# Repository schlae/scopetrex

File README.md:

# SCOPETREX
## Vector Gaming on Your Oscilloscope!

**Update 21-August-2024: I learned that the IRQ line on the 65C22 wasn't connected, so I fixed that.
See the section at the bottom for details, or just fab with the latest files and don't worry about it.**

Have you ever wanted to buy a Vectrex, but you can't afford the high prices on
auction sites? Do you already have a hoard of Vectrexes, but want *another*
one? Well now you can build your own!

The SCOPETREX is basically a Vectrex on a single board without a monitor.
To play games, you have to connect it to an oscilloscope or an XY monitor.

This board is not just an exact clone of a Vectrex; it makes a number of
improvements over the original.

* Single +5V power supply, only 500mA (minimum)
* Configurable X and Y size and polarity
* Configurable brightness and video blanking polarity
* Works with a 68A09/68B09 or the more common 68A09E/68B09E
* Works with the AY-3-8912 sound chip or the cheaper AY-3-8910/YM2149F
* Custom controller board which is also compatible with the Vectrex
* Cool art on the board

All of the components are readily available, either from Mouser or from
various brokers in China. The bills of materials include Mouser part numbers.

[Here is the schematic](https://github.com/schlae/scopetrex/blob/master/Scopetrex.pdf).

There are two separate bills of materials. One is configured for people who
wish to build their SCOPETREX with the 68A09/68B09 (no suffix option), and
the other is configured for the 68A09E/68B09E (note the **E** suffix). In
general, the **E** suffix is easier to find and it is less likely to be a
counterfeit part. One caution: the 6809 and 6809E (no A or B) chips are only
rated to 1MHz while the SCOPETREX requires 1.5MHz operation.

[Bill of Materials, 6809 (plain) version](https://github.com/schlae/scopetrex/blob/master/Scopetrex_6809.csv)

[Bill of Materials, 6809E version](https://github.com/schlae/scopetrex/blob/master/Scopetrex_6809E.csv)

Please note that the 0.1" header pins are *not* listed on the BOM. They are
just standard breakaway headers. Jumper shunts (you will need three) are also
not listed on the BOM.

The game cartridge slot is designed to be used with the Sullins EBC18DRAS
(listed in the BOM as S3311-ND) but you can also use the EDAC 395-036-520-202
since it is available from Mouser and it may be more convenient to order all
the parts at once. If you do this, you will need to install the EDAC slot
at a right angle and add 18 bodge wires (see the Assembly Notes section).

[Here are the fab files](https://github.com/schlae/scopetrex/blob/master/fab/Scopetrex.zip).

Board dimensions are 7 x 5 inches. Order the board in whatever cool colors
you like!

## The Controller
The SCOPETREX also has a controller.

[Schematic](https://github.com/schlae/scopetrex/blob/master/controller/controller.pdf)

[Bill of Materials](https://github.com/schlae/scopetrex/blob/master/controller/controller.csv)

[Fab files](https://github.com/schlae/scopetrex/blob/master/controller/fab/controller.zip)

The board is 5.8 x 2 inches. It's very simple, so before fabbing it out,
considering going into Kicad and customizing it to your tastes. Add some fancy
silkscreen artwork or whatever you want.

The thumb joystick is listed with a Digi-Key part number since Mouser doesn't
carry it, but you can also get it from [Sparkfun](https://www.sparkfun.com/products/9032). There are similar joysticks sold by a number of different vendors
but this is the only one that's been tested.

There is a slide switch with 4 positions that selects which button (1 through
4) the top hat control triggers (when you push down on the joystick).

## Firmware
The SCOPETREX will run with the standard Vectrex firmware. Just program it
into the flash memory chip (the AT28C64). Note that the "Vectrex BIOS" ROM that
you may find does not include the MINE STORM game. Often, the "MINE STORM" ROM
comes with the BIOS so you should use that instead. I will not tell you where
to get ROMs, nor will I send you any. You could go buy a broken Vectrex and
transplant the ROM from that.

## Assembly Notes

In general it is a good idea to socket the chips that are hard to find and
thus may be counterfeit. It makes troubleshooting much easier. Therefore,
consider socketing the 6809, the 65C22, and the AY-3-8910/12.

The U101/MC34063 power supply chip should be soldered directly to the board
for best performance since a socket adds resistance.

The game cartridge connector has two different part numbers on the BOM. If
you ordered the EDAC part from Mouser which is designed to mount vertically
on the board, you will not be able to plug the cart into it because the case
will bump into components on the board. I recommend rotating the connector
90 degrees and soldering the bottom 18 pins directly to the footprint and
connecting the top 18 pins using bodge wires.

Don't forget to install the jumpers J301, J302, and J303. If you aren't sure
what polarity you need, just set them all to "NORM."

Set all the trimmer potentiometers to the halfway position. You'll tune them
later on.

Don't forget to flash the firmware into the AT28C64. There are many devices
that can do this. I like the MINIPRO programmers that are available cheaply
from many different sources.

When you assemble the controller board, be sure to install the DE-9 connector
on the bottom of the circuit board rather than the top.

## Initial Powerup and Calibration
You can connect your oscilloscope probes to the X, Y, and Z (aka blanking)
directly or by making up adapter BNC cables that go directly into your
oscilloscope or XY monitor inputs.

To start with, connect just the X and Y outputs to your oscilloscope's channel
1 and channel 2 inputs. Set both channels to 1V/div and put the oscilloscope
into XY mode (on some oscilloscopes, you do this by rotating the horizontal
sweep rate knob all the way counterclockwise).

**Be very careful about setting the brightness/intensity control on your
oscilloscope. A spot that is too bright can permanently damage the phosphor
coating inside the CRT, leaving a dark spot!**

Connect a 5V power source to the input jack on the SCOPETREX and move the
power switch to the ON position. After a second you should see lines and dots
appear in various places on the oscilloscope. You may have to adjust the
intensity knob to be able to see them.

Next, connect the oscilloscope's Z axis input (sometimes called video or
blanking) to the Z axis output of the SCOPETREX. Try adjusting the brightness
trimmer on the SCOPETREX. If you still see a lot of lines and a bright spot
in the middle of the screen, switch the polarity jumper on the Z axis (JP301).
Adjust the brightness trimmer again until the spot in the center goes away.

At this point you can also plug in a controller and some speakers into the
audio jack. Make sure you can get sound, and check if the controller works.

The SCOPETREX requires some calibration to be performed to get the best image
quality. To do this, you will need a Vectrex test cart (often included in
multicarts, which you probably want to have anyway.)

The first step of calibration involves correcting the DAC offset voltage. With
the test cart installed (no hot swapping carts! label side up!) you will first
see a grid displayed on the screen. Hit button 4, and the display should read
"DAC OFFSET," slowly blinking on and off. Connect a voltmeter between ground
(I like the convenient mounting holes in the corners of the board) and the left
side of R303 (marked with an arrow on the board). This is the voltage output,
pin 1, of the U304 op amp. With the text *off*, the voltmeter should read 0V.
If not, adjust the DAC offset trimmer until you get the voltage to 0V.

The second step involves fixing the X and Y adjustments. You can do this with
the test cart's third screen by pressing button 4 again. You'll see some
diamond-shaped targets; adjust X and Y so that the vertical and horizontal
lines are center inside the diamond shapes.

The third step is less specific, try hitting buttons 3 and 4 to switch to
various screens. Adjust the X and Y as you like to get things to look good.

The final step is the joystick calibration. Go to the last screen--the one
that you can't seem to exit by pushing a button--and adjust the two trimmers
on the *controller board* until the line segment turns into a dot. Swirl the
joystick around to make sure it hits all the square boxes. To exit this screen,
you have to push buttons 1 and 3 or buttons 1 and 4 at the same time.

## XY Monitors

XY monitors such as the Tektronix 602 or 604 offer a nicer experience for
playing Vectrex games. Typically they have a fixed analog deflection voltage of
only a volt or two, so you will need to use the width and height trimmers to
dial back the deflection so that all the objects are on the screen.

Pro tip--turn a landscape-mode XY monitor up on its side and swap the X and Y
inputs to mimic the Vectrex's portrait orientation.

## Troubleshooting
The SCOPETREX is a fairly complex mixed-signal board. I can't tell you all the
possible ways it can go wrong, but here's a list of things to check...
* Power supply voltages: Are +5V, -5V, and the -12V rails all present?
* Reset signal: Does the reset input on the 6809 go high?
* Does the 6809 have a valid set of clock signals? Check E and Q, and the
crystal or oscillator
* Is there activity on the bus? Check the address and data lines
* Does the ROM chip ever get selected? Both the CS# and OE# lines must be
pulsing for that to happen. How about the RAM chip?
* Check for activity on the 65C22 outputs
* Does sound come out of the AY-3-8910/2?
* Look at the waveform on pin 1 of U304A. You should see a fairly complex
waveform
* The SCOPETREX works by using a constant voltage into an integrator to
generate ramps that drive the X and Y deflection signals. Work your way back
along the analog signal chain starting from the individual deflection outputs
* Take a look at the blanking signal (Z axis) output magnitudes. You might
want to check the manual for your oscilloscope to find out the acceptable range
of voltages

## The IRQ Line Bug

Lately it came to my attention that there was a bug in the earlier version of
the board, but nobody actually reported it to me! Fortunately it is a very
easy issue to fix. If you fab your boards from the latest version of the files
in this repository (21-August-2024 or later) then this issue has been fixed.

If you have an older board, you can correct the problem by running a wire from
U207 pin 21 (the 65C22) and U206 pin 3.

## Other Notes

After all that work, don't forget to enjoy playing some Vectrex games!

## License
This work is licensed under a Creative Commons Attribution-ShareAlike 4.0
International License. See [https://creativecommons.org/licenses/by-sa/4.0/](https://creativecommons.org/licenses/by-sa/4.0/).

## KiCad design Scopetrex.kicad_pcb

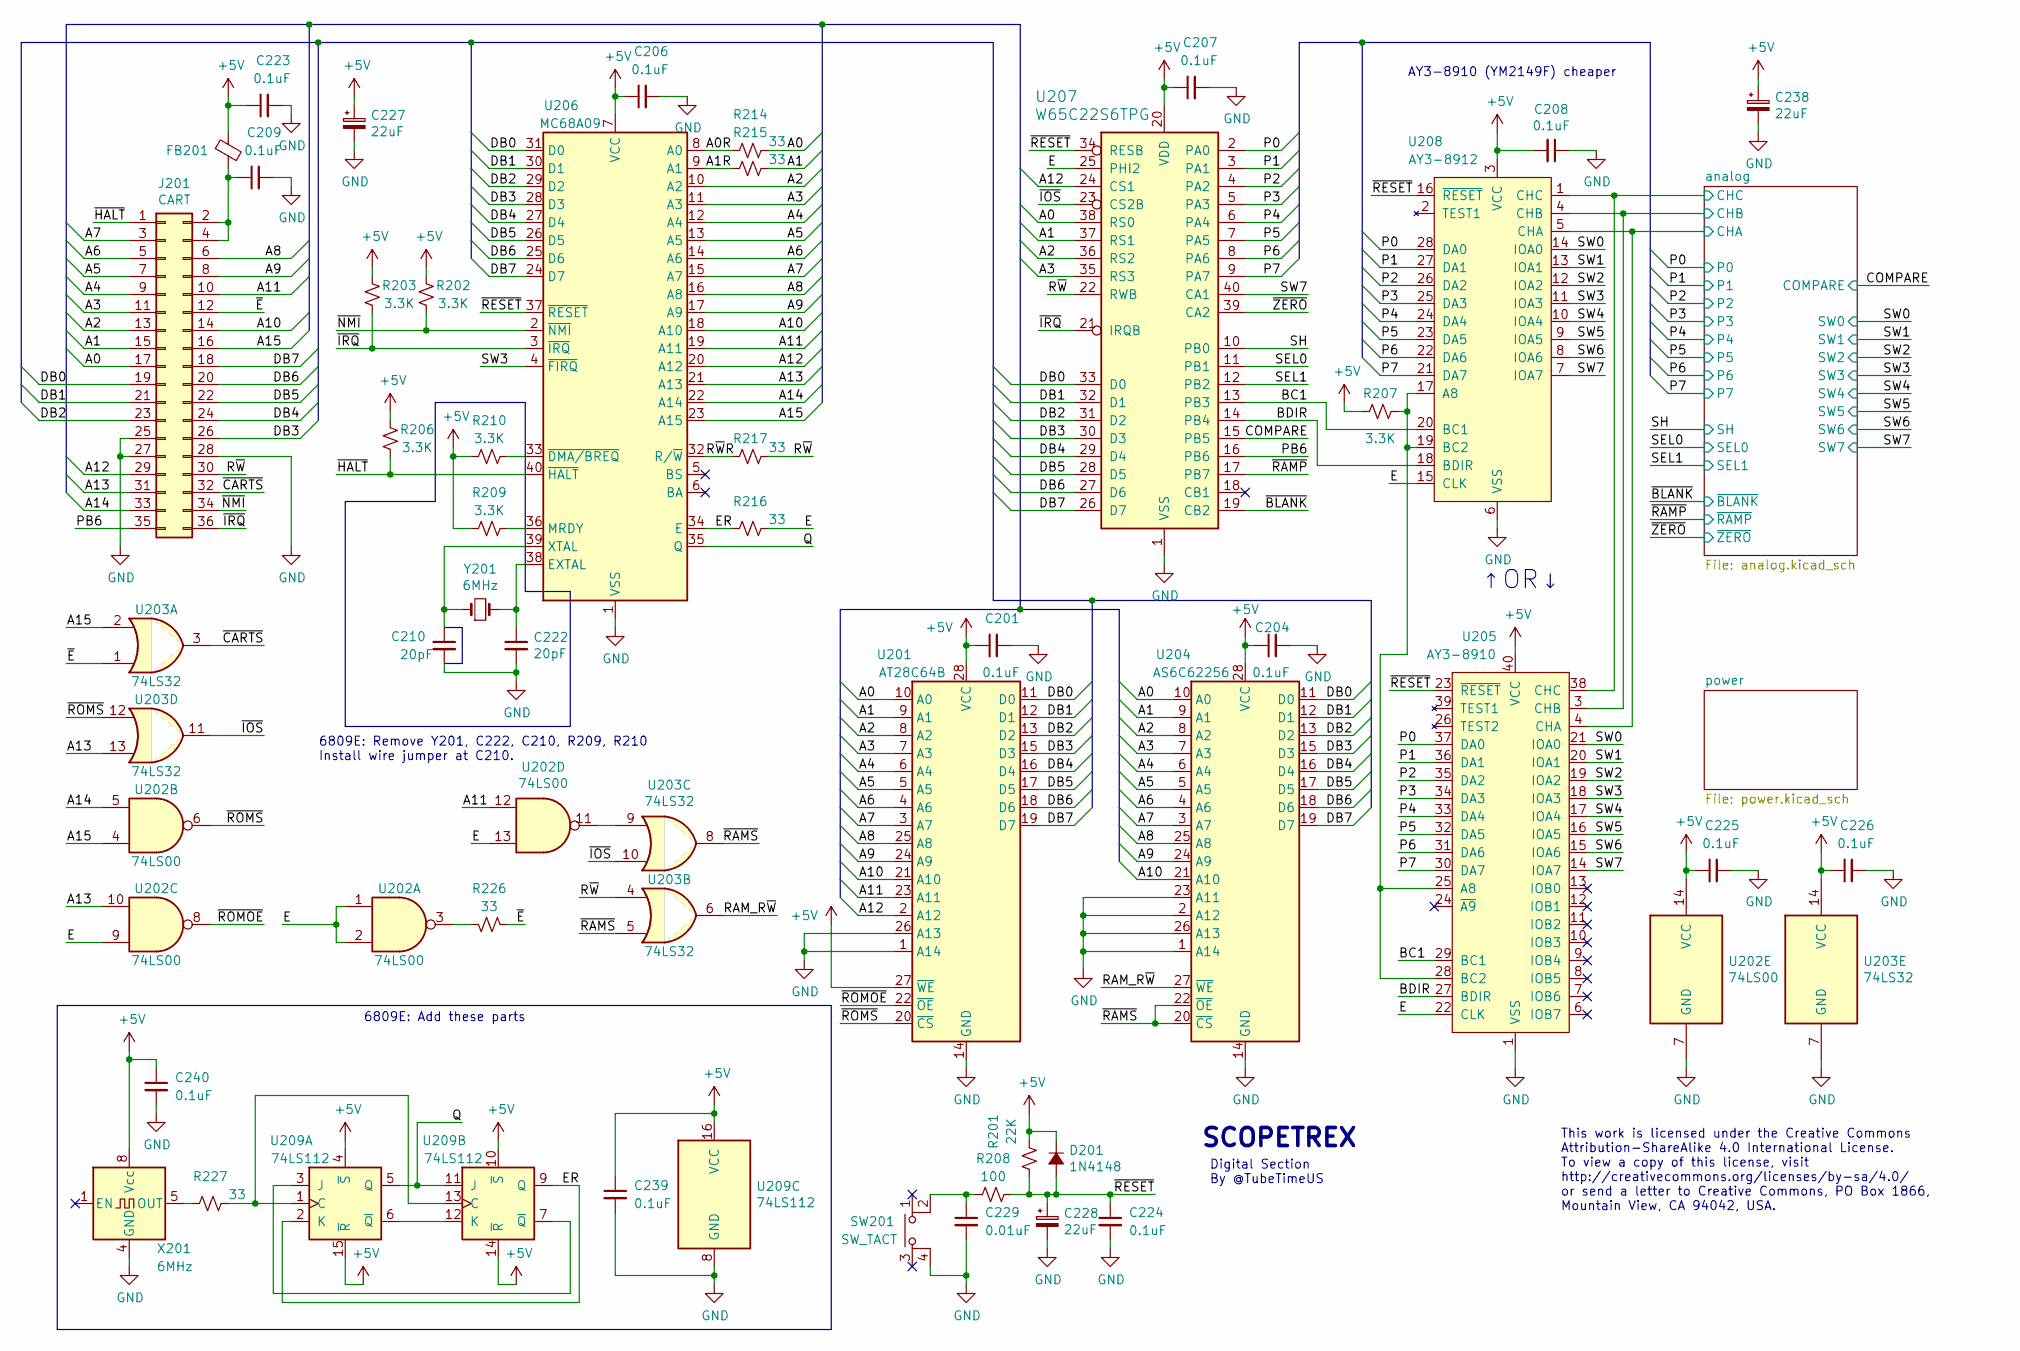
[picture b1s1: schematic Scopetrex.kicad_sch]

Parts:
C201, C204, C206, C207, C208, C209, C223, C224, C225, C226, C239, C240: 0.1uF; C_Disc_D0.2in_W0.1in_P0.2in; Mouser 581-SR215C104K
C210, C222: 20pF; C_Disc_D0.2in_W0.1in_P0.2in; Mouser 581-SR215A220KARTR1
C227, C228, C238: 22uF; CAPAP200; Mouser 647-UPW1A220MDD6TP
C229: 0.01uF; C_Disc_D0.2in_W0.1in_P0.2in; Mouser 581-SR211C103KARTR1
D201: 1N4148; DIOA500; Mouser 512-1N4148
FB201: 96Ω @ 25MHz; FB254; Mouser 623-2743007112
J201: CART; SULLINS_EBC18DRAS; Mouser 587-395-036
R201: 22K; RESA500; Mouser 603-CFR-25JR-5222K
R202, R203, R206, R207, R209, R210: 3.3K; RESA500; Mouser 603-CFR-25JR-523K3
R208: 100; RESA500; Mouser 603-CFR-25JR-52100R
R214, R215, R216, R217, R226, R227: 33; RESA500; Mouser 603-CFR-25JR-5233R
SW201: SW_TACT; ESWITCH_TL1105; Mouser 612-TL1105B
U201: AT28C64B; DIP254P1524X635-28; Mouser 556-AT28C64B15PU
U202: 74LS00; DIP254P762X635-14; Mouser 595-SN74LS00N
U203: 74LS32; DIP254P762X635-14; Mouser 595-SN74LS32N
U204: AS6C62256; DIP254P1524X635-28; Mouser 913-AS6C62256-55PCN
U205: AY3-8910; DIP254P1524X635-40
U206: MC68A09; DIP254P1524X635-40
U207: W65C22S6TPG; DIP254P1524X635-40; Mouser 955-W65C22S6TPG-14
U208: AY3-8912; DIP254P1524X635-28
U209: 74LS112; DIP254P762X635-16; Mouser 595-SN74LS112AN
X201: 6MHz; Oscillator_DIP-8; Mouser 774-MXO45HS-3C-6.0
Y201: 6MHz; Crystal_HC49-4H_Vertical; Mouser 815-AB-6-B2

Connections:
+5V: C201.1, C204.1, C206.1, C207.1, C208.2, C223.1, C225.1, C226.1, C227.1, C238.1, C239.1, C240.1, D201.1 (K), FB201.1, R201.1, R202.2, R203.2, R206.2, R207.2, R209.1, R210.2, U201.27 (~WE), U201.28 (VCC), U202.14 (VCC), U203.14 (VCC), U204.28 (VCC), U205.40 (VCC), U206.7 (VCC), U207.20 (VDD), U208.3 (VCC), U209.4 (~S), U209.10 (~S), U209.14 (~R), U209.15 (~R), U209.16 (VCC), X201.8 (Vcc); also elsewhere on the board
/A0: J201.17, R214.1, U201.10 (A0), U204.10 (A0), U207.38 (RS0)
/A0R: R214.2, U206.8 (A0)
/A1: J201.15, R215.1, U201.9 (A1), U204.9 (A1), U207.37 (RS1)
/A1R: R215.2, U206.9 (A1)
/A2: J201.13, U201.8 (A2), U204.8 (A2), U206.10 (A2), U207.36 (RS2)
/A3: J201.11, U201.7 (A3), U204.7 (A3), U206.11 (A3), U207.35 (RS3)
/A4: J201.9, U201.6 (A4), U204.6 (A4), U206.12 (A4)
/A5: J201.7, U201.5 (A5), U204.5 (A5), U206.13 (A5)
/A6: J201.5, U201.4 (A6), U204.4 (A6), U206.14 (A6)
/A7: J201.3, U201.3 (A7), U204.3 (A7), U206.15 (A7)
/A8: J201.6, U201.25 (A8), U204.25 (A8), U206.16 (A8)
/A9: J201.8, U201.24 (A9), U204.24 (A9), U206.17 (A9)
/A10: J201.14, U201.21 (A10), U204.21 (A10), U206.18 (A10)
/A11: J201.10, U201.23 (A11), U202.12, U206.19 (A11)
/A12: J201.29, U201.2 (A12), U206.20 (A12), U207.24 (CS1)
/A13: J201.31, U202.10, U203.13, U206.21 (A13)
/A14: J201.33, U202.5, U206.22 (A14)
/A15: J201.16, U202.4, U203.2, U206.23 (A15)
/BC1: U205.29 (BC1), U207.13 (PB3), U208.20 (BC1)
/BDIR: U205.27 (BDIR), U207.14 (PB4), U208.18 (BDIR)
/COMPARE: U207.15 (PB5); also elsewhere on the board
/DB0: J201.19, U201.11 (D0), U204.11 (D0), U206.31 (D0), U207.33 (D0)
/DB1: J201.21, U201.12 (D1), U204.12 (D1), U206.30 (D1), U207.32 (D1)
/DB2: J201.23, U201.13 (D2), U204.13 (D2), U206.29 (D2), U207.31 (D2)
/DB3: J201.26, U201.15 (D3), U204.15 (D3), U206.28 (D3), U207.30 (D3)
/DB4: J201.24, U201.16 (D4), U204.16 (D4), U206.27 (D4), U207.29 (D4)
/DB5: J201.22, U201.17 (D5), U204.17 (D5), U206.26 (D5), U207.28 (D5)
/DB6: J201.20, U201.18 (D6), U204.18 (D6), U206.25 (D6), U207.27 (D6)
/DB7: J201.18, U201.19 (D7), U204.19 (D7), U206.24 (D7), U207.26 (D7)
/E: R216.1, U202.1, U202.2, U202.9, U202.13, U205.22 (CLK), U207.25 (PHI2), U208.15 (CLK)
/ER: R216.2, U206.34 (E), U209.2 (K), U209.9 (Q)
/P0: U205.37 (DA0), U207.2 (PA0), U208.28 (DA0); also elsewhere on the board
/P1: U205.36 (DA1), U207.3 (PA1), U208.27 (DA1); also elsewhere on the board
/P2: U205.35 (DA2), U207.4 (PA2), U208.26 (DA2); also elsewhere on the board
/P3: U205.34 (DA3), U207.5 (PA3), U208.25 (DA3); also elsewhere on the board
/P4: U205.33 (DA4), U207.6 (PA4), U208.24 (DA4); also elsewhere on the board
/P5: U205.32 (DA5), U207.7 (PA5), U208.23 (DA5); also elsewhere on the board
/P6: U205.31 (DA6), U207.8 (PA6), U208.22 (DA6); also elsewhere on the board
/P7: U205.30 (DA7), U207.9 (PA7), U208.21 (DA7); also elsewhere on the board
/PB6: J201.35, U207.16 (PB6)
/Q: U206.35 (Q), U209.5 (Q), U209.11 (J)
/RAM_R~W: U203.6, U204.27 (~WE)
/R~W: J201.30, R217.1, U203.4, U207.22 (RWB)
/R~W~R: R217.2, U206.32 (R/~W)
/SEL0: U207.11 (PB1); also elsewhere on the board
/SEL1: U207.12 (PB2); also elsewhere on the board
/SH: U207.10 (PB0); also elsewhere on the board
/SW0: U205.21 (IOA0), U208.14 (IOA0); also elsewhere on the board
/SW1: U205.20 (IOA1), U208.13 (IOA1); also elsewhere on the board
/SW2: U205.19 (IOA2), U208.12 (IOA2); also elsewhere on the board
/SW3: U205.18 (IOA3), U206.4 (~FIRQ), U208.11 (IOA3); also elsewhere on the board
/SW4: U205.17 (IOA4), U208.10 (IOA4); also elsewhere on the board
/SW5: U205.16 (IOA5), U208.9 (IOA5); also elsewhere on the board
/SW6: U205.15 (IOA6), U208.8 (IOA6); also elsewhere on the board
/SW7: U205.14 (IOA7), U207.40 (CA1), U208.7 (IOA7); also elsewhere on the board
/analog/CHA: U205.4 (CHA), U208.5 (CHA); also elsewhere on the board
/analog/CHB: U205.3 (CHB), U208.4 (CHB); also elsewhere on the board
/analog/CHC: U205.38 (CHC), U208.1 (CHC); also elsewhere on the board
/~BLANK: U207.19 (CB2); also elsewhere on the board
/~CARTS: J201.32, U203.3
/~E: J201.12, R226.2, U203.1
/~HALT: J201.1, R206.1, U206.40 (~HALT)
/~IOS: U203.10, U203.11, U207.23 (CS2B)
/~IRQ: J201.36, R203.1, U206.3 (~IRQ), U207.21 (IRQB)
/~NMI: J201.34, R202.1, U206.2 (~NMI)
/~RAMP: U207.17 (PB7); also elsewhere on the board
/~RAMS: U203.5, U203.8, U204.20 (~CS), U204.22 (~OE)
/~RESET: C224.1, C228.1, D201.2 (A), R201.2, R208.1, U205.23 (~RESET), U206.37 (~RESET), U207.34 (RESB), U208.16 (~RESET)
/~ROMOE: U201.22 (~OE), U202.8
/~ROMS: U201.20 (~CS), U202.6, U203.12
/~ZERO: U207.39 (CA2); also elsewhere on the board
GND: C201.2, C204.2, C206.2, C207.2, C208.1, C209.2, C210.2, C222.2, C223.2, C224.2, C225.2, C226.2, C227.2, C228.2, C229.2, C238.2, C239.2, C240.2, J201.25, J201.27, J201.28, SW201.4, U201.1 (A14), U201.14 (GND), U201.26 (A13), U202.7 (GND), U203.7 (GND), U204.1 (A14), U204.2 (A12), U204.14 (GND), U204.23 (A11), U204.26 (A13), U205.1 (VSS), U206.1 (VSS), U207.1 (VSS), U208.6 (VSS), U209.8 (GND), X201.4 (GND); also elsewhere on the board
unnamed: C209.1, FB201.2, J201.2, J201.4
unnamed: C210.1, U206.39 (XTAL), Y201.1
unnamed: C222.1, U206.38 (EXTAL), Y201.2
unnamed: C229.1, R208.2, SW201.2
unnamed: R207.1, U205.25 (A8), U205.28 (BC2), U208.17 (A8), U208.19 (BC2)
unnamed: R209.2, U206.36 (MRDY)
unnamed: R210.1, U206.33 (~DMA/BREQ)
unnamed: R226.1, U202.3
unnamed: R227.1, U209.1 (C), U209.13 (C)
unnamed: R227.2, X201.5 (OUT)
unnamed: U202.11, U203.9
unnamed: U209.3 (J), U209.7 (~Q)
unnamed: U209.6 (~Q), U209.12 (K)

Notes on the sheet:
6809E: Remove Y201, C222, C210, R209, R210 Install wire jumper at C210.
Digital Section By @TubeTimeUS
SCOPETREX
6809E: Add these parts
↑OR↓
This work is licensed under the Creative Commons Attribution-ShareAlike 4.0 International License. To view a copy of this license, visit http://creativecommons.org/licenses/by-sa/4.0/ or send a letter to Creative Commons, PO Box 1866, Mountain View, CA 94042, USA.
AY3-8910 (YM2149F) cheaper

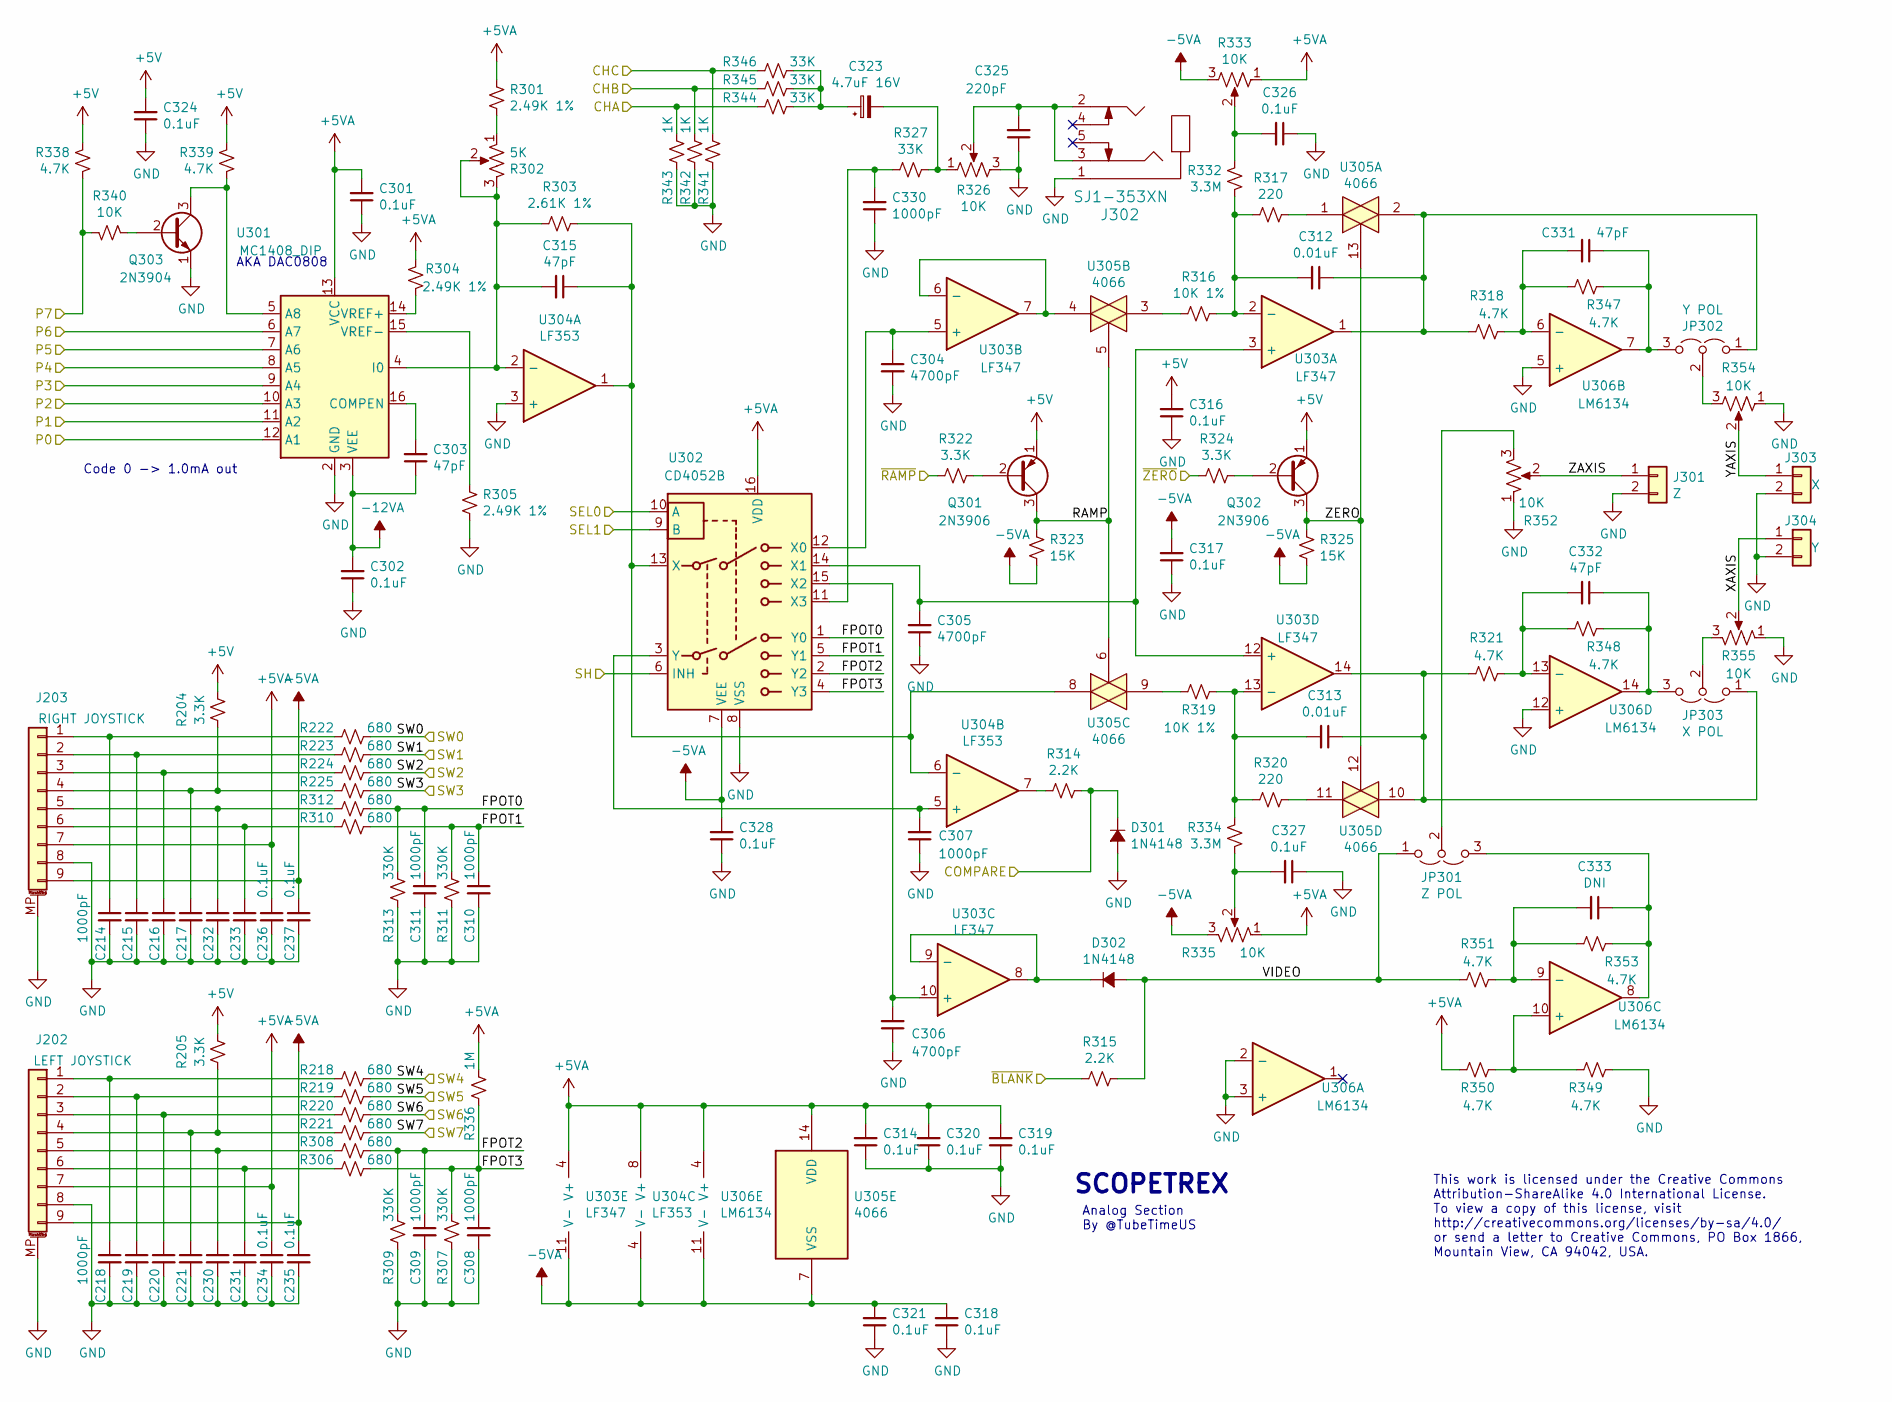
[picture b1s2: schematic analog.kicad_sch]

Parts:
C214, C215, C216, C217, C218, C219, C220, C221, C230, C231, C232, C233, C307, C308, C309, C310, C311, C330: 1000pF; C_Disc_D0.2in_W0.1in_P0.2in; Mouser 581-SR211A102JAR
C234, C235, C236, C237, C301, C302, C314, C316, C317, C318, C319, C320, C321, C324, C326, C327, C328: 0.1uF; C_Disc_D0.2in_W0.1in_P0.2in; Mouser 581-SR215C104K
C303, C315, C331, C332: 47pF; C_Disc_D0.2in_W0.1in_P0.2in; Mouser 581-SR211A470JAR
C304, C305, C306: 4700pF; C_Disc_D0.2in_W0.1in_P0.2in; Mouser 810-FG28C0G2A472JRT6
C312, C313: 0.01uF; CAPF500P1000X1200; Mouser 810-FG28C0G2A103JRT6
C323: 4.7uF 16V; CAPAE200P500X1100; Mouser 647-UKT1E4R7MDD1TD
C325: 220pF; C_Disc_D0.2in_W0.1in_P0.2in; Mouser 581-SR211A221JAATR
C333: DNI; C_Disc_D0.2in_W0.1in_P0.2in
D301, D302: 1N4148; DIOA500; Mouser 512-1N4148
J202: LEFT JOYSTICK; DB9MC; Mouser 806-K22X-E9P-N
J203: RIGHT JOYSTICK; DB9MC; Mouser 806-K22X-E9P-N
J301: Z; Pin_Header_Straight_1x02_Pitch2.54mm
J302: SJ1-353XN; CUI_SJ1-353XN; Mouser 490-SJ1-3533NG
J303: X; Pin_Header_Straight_1x02_Pitch2.54mm
J304: Y; Pin_Header_Straight_1x02_Pitch2.54mm
JP301: Z POL; Pin_Header_Straight_1x03_Pitch2.54mm
JP302: Y POL; Pin_Header_Straight_1x03_Pitch2.54mm
JP303: X POL; Pin_Header_Straight_1x03_Pitch2.54mm
Q301, Q302: 2N3906; TO92-IL; Mouser 512-2N3906TA
Q303: 2N3904; TO92-IL; Mouser 512-2N3904TA
R204, R205, R322, R324: 3.3K; RESA500; Mouser 603-CFR-25JR-523K3
R218, R219, R220, R221, R222, R223, R224, R225, R306, R308, R310, R312: 680; RESA500; Mouser 603-CFR-25JR-52-680R
R301, R304, R305: 2.49K 1%; RESA500; Mouser 603-MFR-25FRF522K49
R302: 5K; PIHER_PT10_H01; Mouser 531-PT10H-5K-S
R303: 2.61K 1%; RESA500; Mouser 603-MFR-25FRF52-2K61
R307, R309, R311, R313: 330K; RESA500; Mouser 603-CFR-25JR-52-330K
R314, R315: 2.2K; RESA500; Mouser 603-CFR-25JR-522K2
R316, R319: 10K 1%; RESA500; Mouser 603-MFR-25FRF5210K
R317, R320: 220; RESA500; Mouser 603-CFR-25JR-52220R
R318, R321, R338, R339, R347, R348, R349, R350, R351, R353: 4.7K; RESA500; Mouser 603-CFR-25JR-524K7
R323, R325: 15K; RESA500; Mouser 603-CFR-25JR-5215K
R326, R333, R335, R352, R354, R355: 10K; PIHER_PT10_H01; Mouser 531-PT10H-10K-S
R327, R344, R345, R346: 33K; RESA500; Mouser 603-CFR-25JR-52-33K
R332, R334: 3.3M; RESA500; Mouser 603-MFR-25FTE52-3M3
R336: 1M; RESA500; Mouser 603-CFR-25JR-521M
R340: 10K; RESA500; Mouser 603-CFR-25JR-5210K
R341, R342, R343: 1K; RESA500; Mouser 603-CFR-25JR-521K
U301: MC1408_DIP; DIP254P762X635-16; Mouser 926-DAC0808LCN/NOPB
U302: CD4052B; DIP254P762X635-16; Mouser 595-CD4052BE
U303: LF347; DIP254P762X635-14; Mouser 595-LF347N
U304: LF353; DIP254P762X635-8; Mouser 595-LF353P
U305: 4066; DIP254P762X635-14; Mouser 595-CD4066BE
U306: LM6134; DIP254P762X635-14; Mouser 926-LM6134BIN/NOPB

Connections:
+5V: C316.2, C324.2, Q301.1 (E), Q302.1 (E), R204.1, R205.1, R338.2, R339.2; also elsewhere on the board
+5VA: C234.1, C236.1, C301.2, C314.2, C319.2, C320.2, J202.7, J203.7, R301.2, R304.2, R333.1, R335.1, R336.1, R350.2, U301.13 (VCC), U302.16 (VDD), U303.4 (V+), U304.8 (V+), U305.14 (VDD), U306.4 (V+); also elsewhere on the board
-5VA: C235.1, C237.1, C317.2, C318.2, C321.2, C328.2, J202.9, J203.9, R323.2, R325.2, R333.3, R335.3, U302.7 (VEE), U303.11 (V-), U304.4 (V-), U305.7 (VSS), U306.11 (V-); also elsewhere on the board
-12VA: C302.2, C303.1, U301.3 (VEE); also elsewhere on the board
/COMPARE: D301.1 (K), R314.1; also elsewhere on the board
/P0: U301.12 (A1); also elsewhere on the board
/P1: U301.11 (A2); also elsewhere on the board
/P2: U301.10 (A3); also elsewhere on the board
/P3: U301.9 (A4); also elsewhere on the board
/P4: U301.8 (A5); also elsewhere on the board
/P5: U301.7 (A6); also elsewhere on the board
/P6: U301.6 (A7); also elsewhere on the board
/P7: R338.1, R340.1; also elsewhere on the board
/SEL0: U302.10 (A); also elsewhere on the board
/SEL1: U302.9 (B); also elsewhere on the board
/SH: U302.6 (INH); also elsewhere on the board
/SW0: R222.2; also elsewhere on the board
/SW1: R223.2; also elsewhere on the board
/SW2: R224.2; also elsewhere on the board
/SW3: R225.2; also elsewhere on the board
/SW4: R218.2; also elsewhere on the board
/SW5: R219.2; also elsewhere on the board
/SW6: R220.2; also elsewhere on the board
/SW7: R221.2; also elsewhere on the board
/analog/CHA: R343.1, R344.2; also elsewhere on the board
/analog/CHB: R342.1, R345.2; also elsewhere on the board
/analog/CHC: R341.1, R346.2; also elsewhere on the board
/analog/FPOT0: C311.1, R312.2, R313.1, U302.1 (Y0)
/analog/FPOT1: C310.1, R310.2, R311.1, U302.5 (Y1)
/analog/FPOT2: C309.1, R308.2, R309.1, U302.2 (Y2)
/analog/FPOT3: C308.1, R306.2, R307.1, R336.2, U302.4 (Y3)
/analog/RAMP: Q301.3 (C), R323.1, U305.5, U305.6
/analog/VIDEO: D302.2 (A), JP301.1 (A), R315.1, R351.1
/analog/XAXIS: J304.1, R355.2
/analog/YAXIS: J303.1, R354.2
/analog/ZAXIS: J301.1, R352.2
/analog/ZERO: Q302.3 (C), R325.1, U305.12, U305.13
/~BLANK: R315.2; also elsewhere on the board
/~RAMP: R322.2; also elsewhere on the board
/~ZERO: R324.2; also elsewhere on the board
GND: C214.2, C215.2, C216.2, C217.2, C218.2, C219.2, C220.2, C221.2, C230.2, C231.2, C232.2, C233.2, C234.2, C235.2, C236.2, C237.2, C301.1, C302.1, C304.2, C305.1, C306.1, C307.1, C308.2, C309.2, C310.2, C311.2, C314.1, C316.1, C317.1, C318.1, C319.1, C320.1, C321.1, C324.1, C325.1, C326.1, C327.1, C328.1, C330.1, D301.2 (A), J202.8, J202.MP (MountPin), J203.8, J203.MP (MountPin), J301.2, J302.1, J303.2, J304.2, Q303.1 (E), R305.1, R307.2, R309.2, R311.2, R313.2, R326.3, R341.2, R342.2, R343.2, R349.1, R352.1, R354.1, R355.1, U301.2 (GND), U302.8 (VSS), U304.3 (+), U306.2 (-), U306.3 (+), U306.5 (+), U306.12 (+); also elsewhere on the board
unnamed: C214.1, J203.1, R222.1
unnamed: C215.1, J203.2, R223.1
unnamed: C216.1, J203.3, R224.1
unnamed: C217.1, J203.4, R204.2, R225.1
unnamed: C218.1, J202.1, R218.1
unnamed: C219.1, J202.2, R219.1
unnamed: C220.1, J202.3, R220.1
unnamed: C221.1, J202.4, R205.2, R221.1
unnamed: C230.1, J202.5, R308.1
unnamed: C231.1, J202.6, R306.1
unnamed: C232.1, J203.5, R312.1
unnamed: C233.1, J203.6, R310.1
unnamed: C303.2, U301.16 (COMPEN)
unnamed: C304.1, U302.12 (X0), U303.5 (+)
unnamed: C305.2, U302.14 (X1), U303.3 (+), U303.12 (+)
unnamed: C306.2, U302.15 (X2), U303.10 (+)
unnamed: C307.2, U302.3 (Y), U304.5 (+)
unnamed: C312.1, JP302.1 (A), R318.2, U303.1, U305.2
unnamed: C312.2, R316.1, R317.2, R332.1, U303.2 (-)
unnamed: C313.1, JP303.1 (A), R321.1, U303.14, U305.10
unnamed: C313.2, R319.1, R320.2, R334.2, U303.13 (-)
unnamed: C315.1, R303.1, U302.13 (X), U304.1, U304.6 (-), U305.8
unnamed: C315.2, R302.2, R302.3, R303.2, U301.4 (I0), U304.2 (-)
unnamed: C323.1, R344.1, R345.1, R346.1
unnamed: C323.2, R326.1, R327.1
unnamed: C325.2, J302.2, J302.3, R326.2
unnamed: C326.2, R332.2, R333.2
unnamed: C327.2, R334.1, R335.2
unnamed: C330.2, R327.2, U302.11 (X3)
unnamed: C331.1, JP302.3 (B), R347.1, U306.7
unnamed: C331.2, R318.1, R347.2, U306.6 (-)
unnamed: C332.1, JP303.3 (B), R348.2, U306.14
unnamed: C332.2, R321.2, R348.1, U306.13 (-)
unnamed: C333.1, JP301.3 (B), R353.2, U306.8
unnamed: C333.2, R351.2, R353.1, U306.9 (-)
unnamed: D302.1 (K), U303.8, U303.9 (-)
unnamed: JP301.2 (C), R352.3
unnamed: JP302.2 (C), R354.3
unnamed: JP303.2 (C), R355.3
unnamed: Q301.2 (B), R322.1
unnamed: Q302.2 (B), R324.1
unnamed: Q303.2 (B), R340.2
unnamed: Q303.3 (C), R339.1, U301.5 (A8)
unnamed: R301.1, R302.1
unnamed: R304.1, U301.14 (VREF+)
unnamed: R305.2, U301.15 (VREF-)
unnamed: R314.2, U304.7
unnamed: R316.2, U305.3
unnamed: R317.1, U305.1
unnamed: R319.2, U305.9
unnamed: R320.1, U305.11
unnamed: R349.2, R350.1, U306.10 (+)
unnamed: U303.6 (-), U303.7, U305.4

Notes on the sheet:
Analog Section By @TubeTimeUS
AKA DAC0808
Code 0 -> 1.0mA out
SCOPETREX
This work is licensed under the Creative Commons Attribution-ShareAlike 4.0 International License. To view a copy of this license, visit http://creativecommons.org/licenses/by-sa/4.0/ or send a letter to Creative Commons, PO Box 1866, Mountain View, CA 94042, USA.

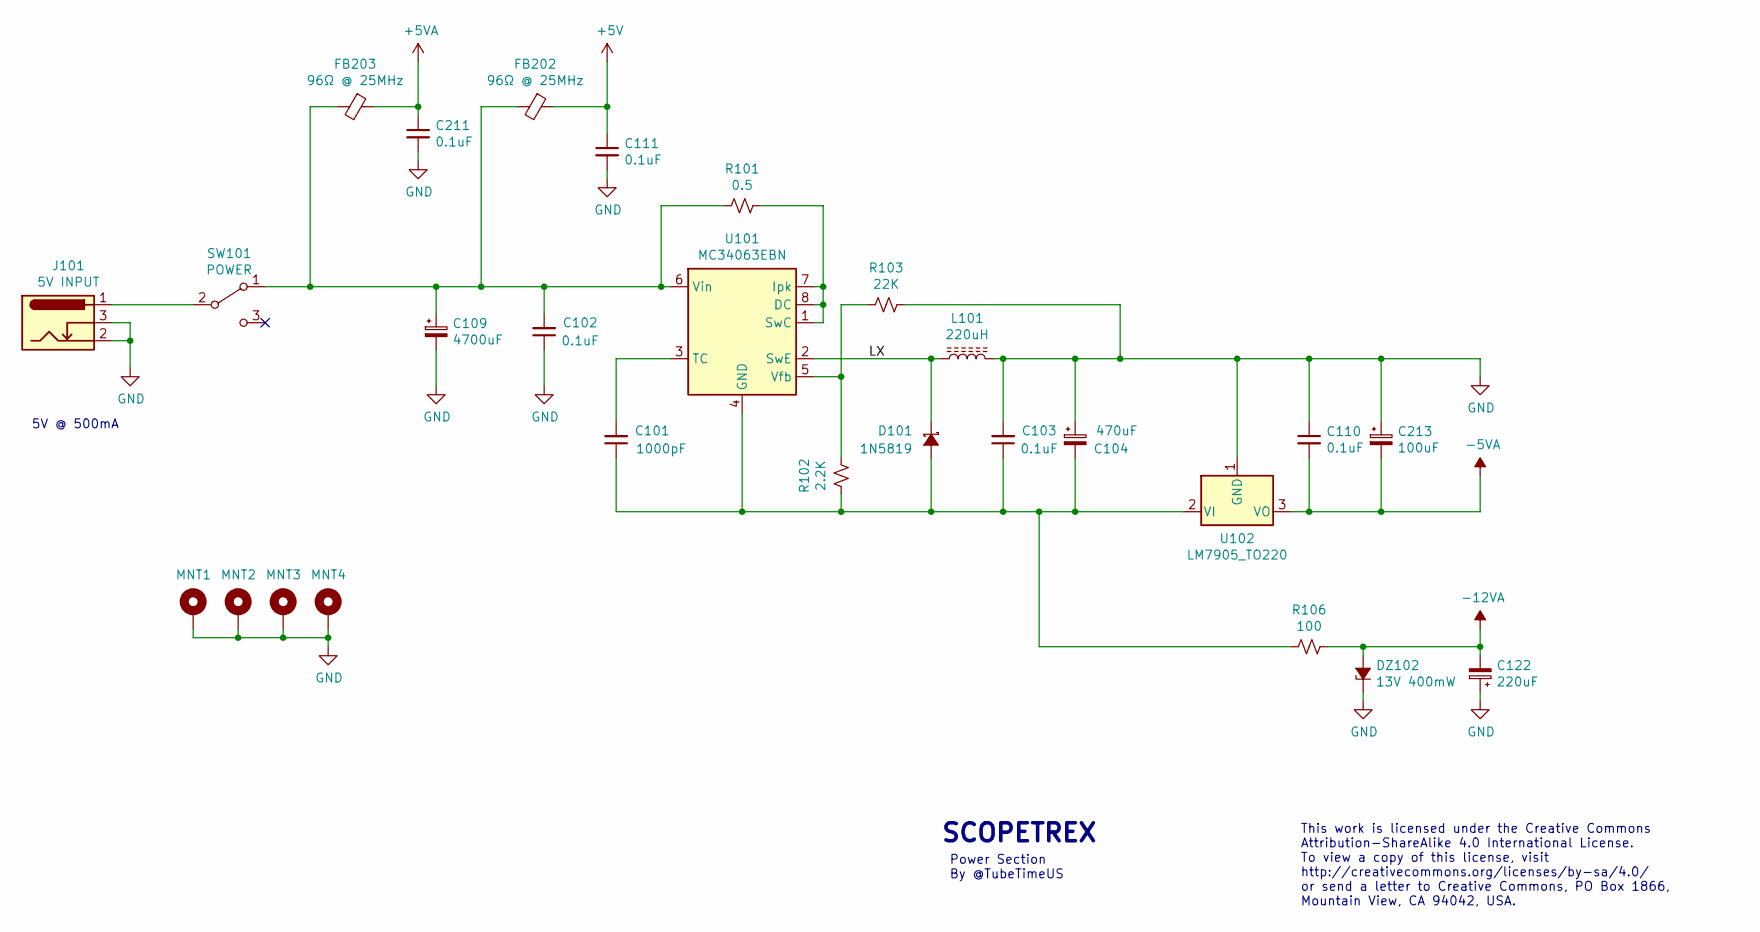
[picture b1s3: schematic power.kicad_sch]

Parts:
C101: 1000pF; C_Disc_D0.2in_W0.1in_P0.2in; Mouser 581-SR211A102JAR
C102, C103, C110, C111, C211: 0.1uF; C_Disc_D0.2in_W0.1in_P0.2in; Mouser 581-SR215C104K
C104: 470uF; CAPAE500P1000X1500; Mouser 80-ESL477M025AH9AA
C109: 4700uF; CAPAE750P1600X2500; Mouser 667-EEU-FS1C472S
C122: 220uF; CAPAE250P630X1100; Mouser 647-UVY1E221MED1TD
C213: 100uF; CAPAE200P500X1100; Mouser 647-UVY1E101MDD1TD
D101: 1N5819; DIOA500; Mouser 511-1N5819
DZ102: 13V 400mW; DIOA500; Mouser 512-1N4743ATR
FB202, FB203: 96Ω @ 25MHz; FB254; Mouser 623-2743007112
J101: 5V INPUT; CUI_PJ-002B; Mouser 490-PJ-002B
L101: 220uH; INDA500P780X750; Mouser 851-RCR875DNP-221K
MNT1, MNT2, MNT3, MNT4: MountingHole_Pad; MountingHole_3.5mm_Pad
R101: 0.5; RESA500; Mouser 660-CF1/4CR50J
R102: 2.2K; RESA500; Mouser 603-CFR-25JR-522K2
R103: 22K; RESA500; Mouser 603-CFR-25JR-5222K
R106: 100; RESA500; Mouser 603-CFR-25JR-52100R
SW101: POWER; NKK_CS12ANW03; Mouser 633-CS12ANW03
U101: MC34063EBN; DIP254P762X635-8; Mouser 511-MC34063EBN
U102: LM7905_TO220; TO-220-3_Vertical; Mouser 926-LM7905CT/NOPB

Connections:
+5V: C111.1, FB202.1; also elsewhere on the board
+5VA: C211.1, FB203.1; also elsewhere on the board
-5VA: C110.2, C213.2, U102.3 (VO); also elsewhere on the board
-12VA: C122.2, DZ102.2 (A), R106.1; also elsewhere on the board
/power/LX: D101.1 (K), L101.1, U101.2 (SwE)
GND: C102.1, C103.2, C104.1, C109.2, C110.1, C111.2, C122.1, C211.2, C213.1, DZ102.1 (K), J101.2, J101.3, L101.2, MNT1.1, MNT2.1, MNT3.1, MNT4.1, R103.1, U102.1 (GND); also elsewhere on the board
unnamed: C101.1, C103.1, C104.2, D101.2 (A), R102.2, R106.2, U101.4 (GND), U102.2 (VI)
unnamed: C101.2, U101.3 (TC)
unnamed: C102.2, C109.1, FB202.2, FB203.2, R101.2, SW101.1 (A), U101.6 (Vin)
unnamed: J101.1, SW101.2 (B)
unnamed: R101.1, U101.1 (SwC), U101.7 (Ipk), U101.8 (DC)
unnamed: R102.1, R103.2, U101.5 (Vfb)

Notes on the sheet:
Power Section By @TubeTimeUS
This work is licensed under the Creative Commons Attribution-ShareAlike 4.0 International License. To view a copy of this license, visit http://creativecommons.org/licenses/by-sa/4.0/ or send a letter to Creative Commons, PO Box 1866, Mountain View, CA 94042, USA.
SCOPETREX
5V @ 500mA

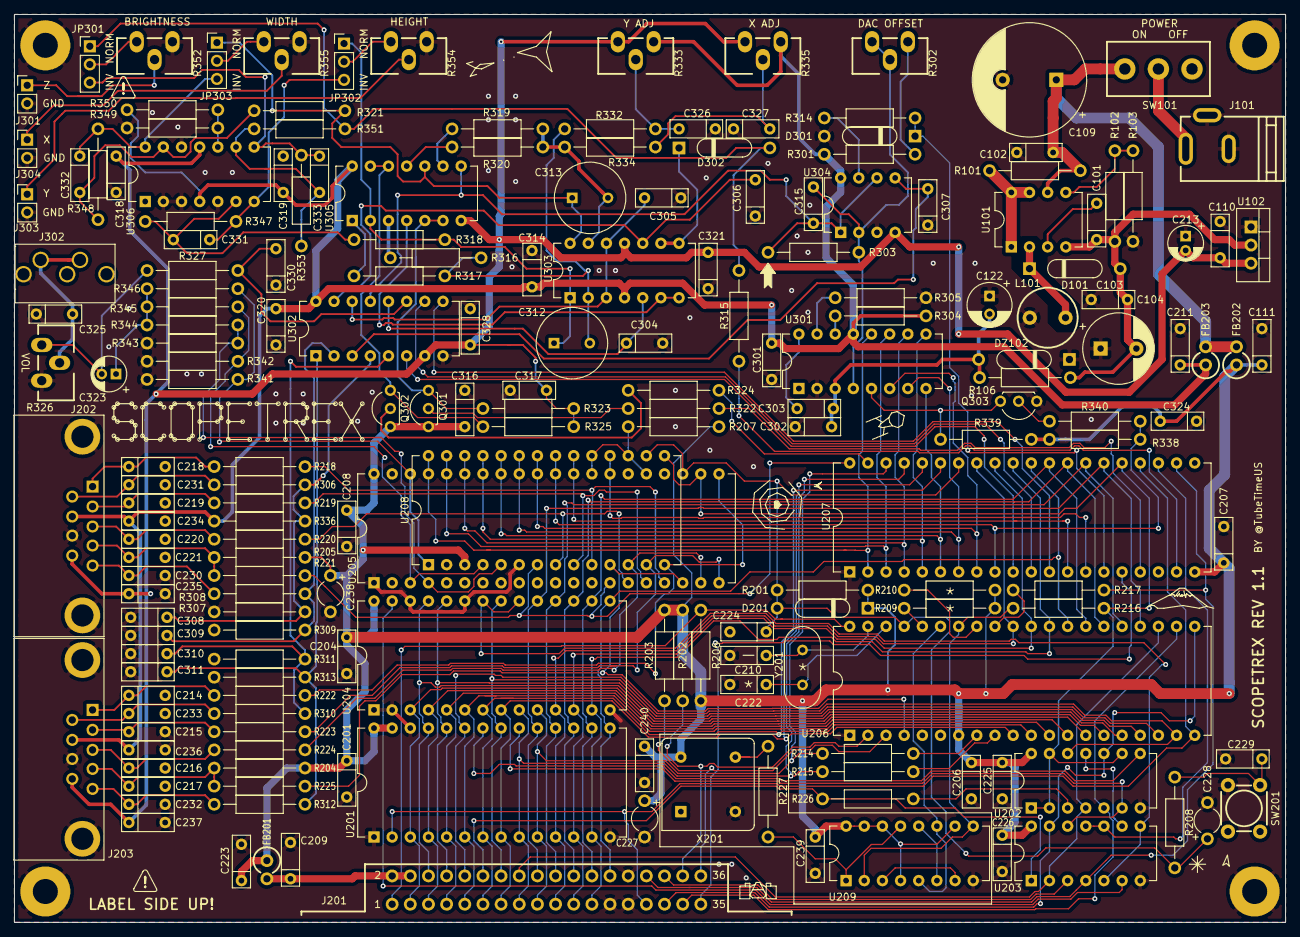
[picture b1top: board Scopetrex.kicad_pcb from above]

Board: 2 copper layers, 177.8 x 127.0 mm, 201 parts (0 on the bottom side), 159 nets.

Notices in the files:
Scopetrex.kicad_pcb:
Copyright (C) 2020 Eric Schlaepfer
